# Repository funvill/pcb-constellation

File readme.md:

# LED Constellation Star map

This project is part of the [2023 100 ideas project](https://blog.abluestar.com/projects/2023-100-ideas/), [Idea 012 - LED Constellation Star map](https://blog.abluestar.com/idea012-led-constellation-star-map/)

The idea is to have a map of constellations using addressable RGB LEDs for the stars. Then program the LEDs so that they twinkle, and the brightness and color temperature matches the corresponding star.

I originally started this project thinking it would be an easy 4 hour, one night project but it ended up taking 8 hours. The mouse bites took up 4 hours alone.

The board is panelized in such a way that it can be displayed as a single board with data and power lines snaking through the mouse bites. This allows for the entire panel to be displayed as a single board using a single microcontroller.

The constellations can also be broken out of the panel and used individually. Each of the corners have a grounded though hold that can be sewn into garment, and through holes to connect a microcontroller.

There are 88 commonly recognizable constellations. I could not fit all the constellations on a single board with a reasonable price. I arbitrarily selected 19 constellations in the northern hemisphere that I liked.

As always open to suggestions

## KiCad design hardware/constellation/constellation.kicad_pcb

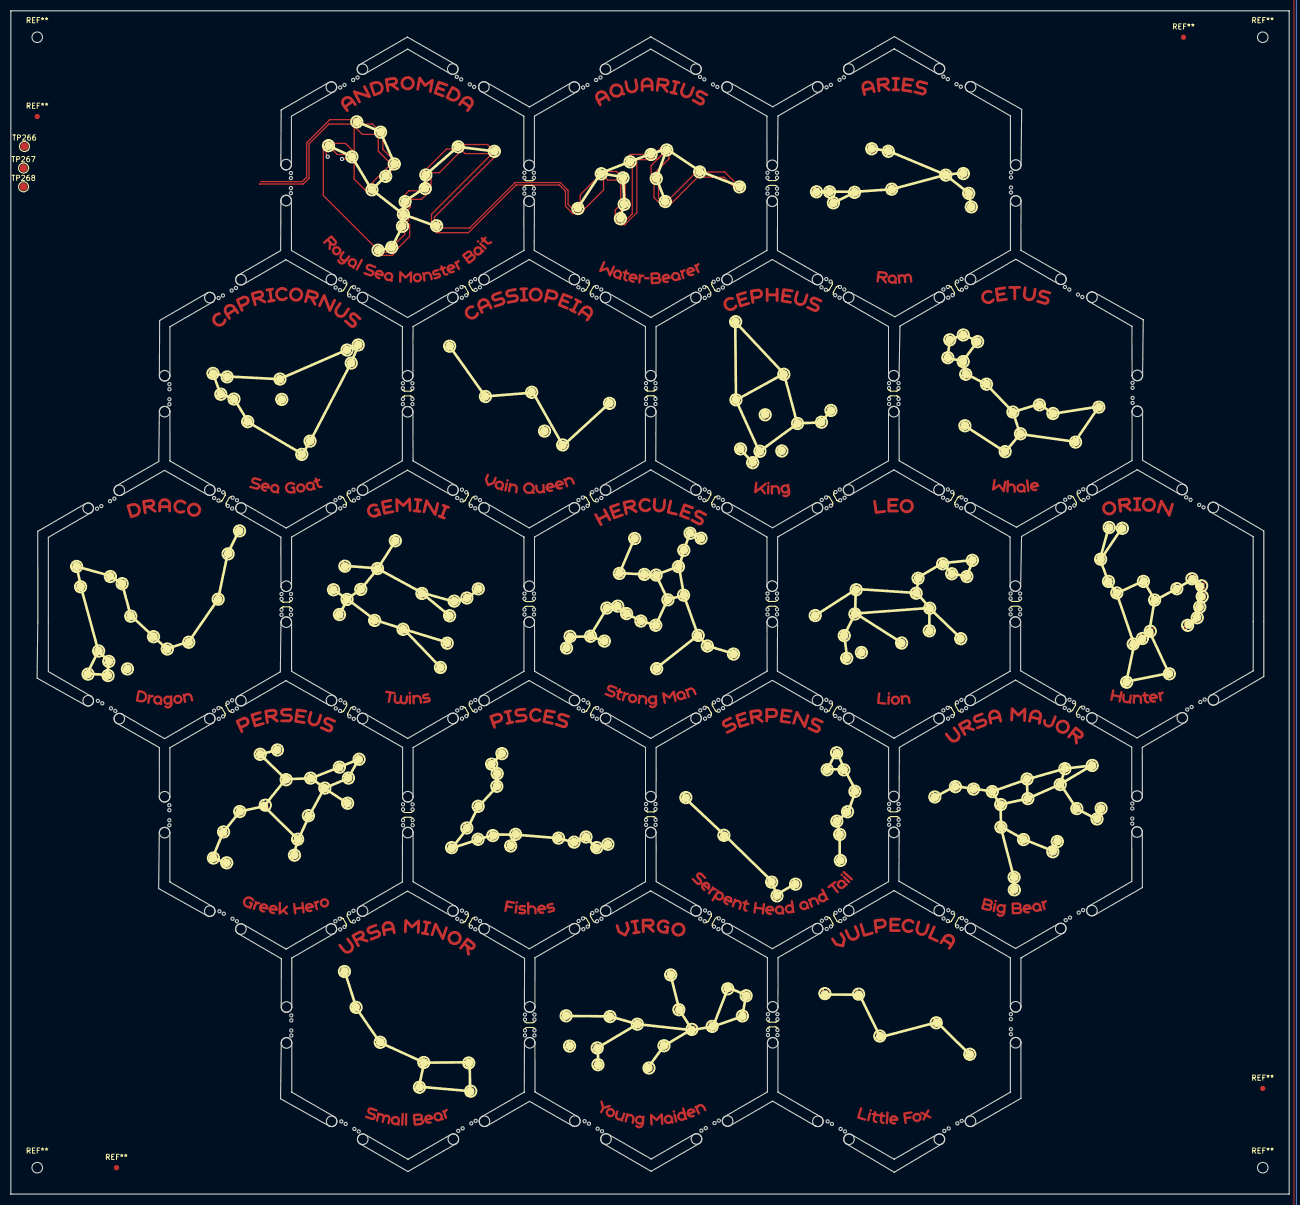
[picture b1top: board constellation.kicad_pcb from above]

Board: 2 copper layers, 242.0 x 224.0 mm, 339 parts (0 on the bottom side), 267 nets.

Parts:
TP266, TP267, TP268: TestPoint; TestPoint_Pad_D1.5mm
U1, U2, U3, U4, U5, U6, U7, U8, U9, U10, U11, U12, U13, U14, U15, U16, U17, U18, U19, U20, U21, U22, U23, U24, U25, U26, U27, U28, U29, U30, U31, U32, U33, U34, U35, U36, U37, U38, U39, U40, U41, U42, U43, U44, U45, U46, U47, U48, U49, U50, U51, U52, U53, U54, U55, U56, U57, U58, U59, U60, U61, U62, U63, U64, U65, U66, U67, U68, U69, U70, U71, U72, U73, U74, U75, U76, U77, U78, U79, U80, U81, U82, U83, U84, U85, U86, U87, U88, U89, U90, U91, U92, U93, U94, U95, U96, U97, U98, U99, U100, U101, U102, U103, U104, U105, U106, U107, U108, U109, U110, U111, U112, U113, U114, U115, U116, U117, U118, U119, U120, U121, U122, U123, U124, U125, U126, U127, U128, U129, U130, U131, U132, U133, U134, U135, U136, U137, U138, U139, U140, U141, U142, U143, U144, U145, U146, U147, U148, U149, U150, U151, U152, U153, U154, U155, U156, U157, U158, U159, U160, U161, U162, U163, U164, U165, U166, U167, U168, U169, U170, U171, U172, U173, U174, U175, U176, U177, U178, U179, U180, U181, U182, U183, U184, U185, U186, U187, U188, U189, U190, U191, U192, U193, U194, U195, U196, U197, U198, U199, U200, U201, U202, U203, U204, U205, U206, U207, U208, U209, U210, U211, U212, U213, U214, U215, U216, U217, U218, U219, U220, U221, U222, U223, U224, U225, U226, U227, U228, U229, U230, U231, U232, U233, U234, U235, U236, U237, U238, U239, U240, U241, U242, U243, U244, U245, U246, U247, U248, U249, U250, U251, U252, U253, U254, U255, U256, U257, U258, U259, U260, U261, U262, U263, U264, U265, U266: XL-1010RGBC; LED-SMD_4P-L1.0-W1.0-TL_XL-1010RGBC-WS2812B
mouse-bite-2mm-slot, mouse-bite-2mm-slot#2, mouse-bite-2mm-slot#8, mouse-bite-2mm-slot#14, mouse-bite-2mm-slot#17, mouse-bite-2mm-slot#18, mouse-bite-2mm-slot#22, mouse-bite-2mm-slot#25, mouse-bite-2mm-slot#28, mouse-bite-2mm-slot#29, mouse-bite-2mm-slot#30, mouse-bite-2mm-slot#33, mouse-bite-2mm-slot#36, mouse-bite-2mm-slot#40, mouse-bite-2mm-slot#41, mouse-bite-2mm-slot#43, mouse-bite-2mm-slot#45, mouse-bite-2mm-slot#47, mouse-bite-2mm-slot#48, mouse-bite-2mm-slot#50, mouse-bite-2mm-slot#56, mouse-bite-2mm-slot#57, mouse-bite-2mm-slot#61, mouse-bite-2mm-slot#64, mouse-bite-2mm-slot#65, mouse-bite-2mm-slot#67, mouse-bite-2mm-slot#68, mouse-bite-2mm-slot#70: VAL**; mouse-bite-2mm-slot_edge
mouse-bite-2mm-slot#3, mouse-bite-2mm-slot#4, mouse-bite-2mm-slot#5, mouse-bite-2mm-slot#6, mouse-bite-2mm-slot#7, mouse-bite-2mm-slot#9, mouse-bite-2mm-slot#10, mouse-bite-2mm-slot#11, mouse-bite-2mm-slot#12, mouse-bite-2mm-slot#13, mouse-bite-2mm-slot#15, mouse-bite-2mm-slot#16, mouse-bite-2mm-slot#19, mouse-bite-2mm-slot#20, mouse-bite-2mm-slot#21, mouse-bite-2mm-slot#23, mouse-bite-2mm-slot#24, mouse-bite-2mm-slot#26, mouse-bite-2mm-slot#27, mouse-bite-2mm-slot#31, mouse-bite-2mm-slot#32, mouse-bite-2mm-slot#34, mouse-bite-2mm-slot#35, mouse-bite-2mm-slot#37, mouse-bite-2mm-slot#38, mouse-bite-2mm-slot#39, mouse-bite-2mm-slot#42, mouse-bite-2mm-slot#44, mouse-bite-2mm-slot#46, mouse-bite-2mm-slot#49, mouse-bite-2mm-slot#51, mouse-bite-2mm-slot#52, mouse-bite-2mm-slot#53, mouse-bite-2mm-slot#54, mouse-bite-2mm-slot#55, mouse-bite-2mm-slot#58, mouse-bite-2mm-slot#59, mouse-bite-2mm-slot#60, mouse-bite-2mm-slot#62, mouse-bite-2mm-slot#63, mouse-bite-2mm-slot#66, mouse-bite-2mm-slot#69: VAL**; mouse-bite-2mm-slot_1

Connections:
+5V: U1.2 (VDD), U2.2 (VDD), U3.2 (VDD), U4.2 (VDD), U5.2 (VDD), U6.2 (VDD), U7.2 (VDD), U8.2 (VDD), U9.2 (VDD), U10.2 (VDD), U11.2 (VDD), U12.2 (VDD), U13.2 (VDD), U14.2 (VDD), U15.2 (VDD), U16.2 (VDD), U17.2 (VDD), U18.2 (VDD), U19.2 (VDD), U20.2 (VDD), U21.2 (VDD), U22.2 (VDD), U23.2 (VDD), U24.2 (VDD), U25.2 (VDD), U26.2 (VDD), U27.2 (VDD), U28.2 (VDD), U29.2 (VDD), U30.2 (VDD), U31.2 (VDD), U32.2 (VDD), U33.2 (VDD), U34.2 (VDD), U35.2 (VDD), U36.2 (VDD), U37.2 (VDD), U38.2 (VDD), U39.2 (VDD), U40.2 (VDD), U41.2 (VDD), U42.2 (VDD), U43.2 (VDD), U44.2 (VDD), U45.2 (VDD), U46.2 (VDD), U47.2 (VDD), U48.2 (VDD), U49.2 (VDD), U50.2 (VDD), U51.2 (VDD), U52.2 (VDD), U53.2 (VDD), U54.2 (VDD), U55.2 (VDD), U56.2 (VDD), U57.2 (VDD), U58.2 (VDD), U59.2 (VDD), U60.2 (VDD), U61.2 (VDD), U62.2 (VDD), U63.2 (VDD), U64.2 (VDD), U65.2 (VDD), U66.2 (VDD), U67.2 (VDD), U68.2 (VDD), U69.2 (VDD), U70.2 (VDD), U71.2 (VDD), U72.2 (VDD), U73.2 (VDD), U74.2 (VDD), U75.2 (VDD), U76.2 (VDD), U77.2 (VDD), U78.2 (VDD), U79.2 (VDD), U80.2 (VDD), U81.2 (VDD), U82.2 (VDD), U83.2 (VDD), U84.2 (VDD), U85.2 (VDD), U86.2 (VDD), U87.2 (VDD), U88.2 (VDD), U89.2 (VDD), U90.2 (VDD), U91.2 (VDD), U92.2 (VDD), U93.2 (VDD), U94.2 (VDD), U95.2 (VDD), U96.2 (VDD), U97.2 (VDD), U98.2 (VDD), U99.2 (VDD), U100.2 (VDD), U101.2 (VDD), U102.2 (VDD), U103.2 (VDD), U104.2 (VDD), U105.2 (VDD), U106.2 (VDD), U107.2 (VDD), U108.2 (VDD), U109.2 (VDD), U110.2 (VDD), U111.2 (VDD), U112.2 (VDD), U113.2 (VDD), U114.2 (VDD), U115.2 (VDD), U116.2 (VDD), U117.2 (VDD), U118.2 (VDD), U119.2 (VDD), U120.2 (VDD), U121.2 (VDD), U122.2 (VDD), U123.2 (VDD), U124.2 (VDD), U125.2 (VDD), U126.2 (VDD), U127.2 (VDD), U128.2 (VDD), U129.2 (VDD), U130.2 (VDD), U131.2 (VDD), U132.2 (VDD), U133.2 (VDD), U134.2 (VDD), U135.2 (VDD), U136.2 (VDD), U137.2 (VDD), U138.2 (VDD), U139.2 (VDD), U140.2 (VDD), U141.2 (VDD), U142.2 (VDD), U143.2 (VDD), U144.2 (VDD), U145.2 (VDD), U146.2 (VDD), U147.2 (VDD), U148.2 (VDD), U149.2 (VDD), U150.2 (VDD), U151.2 (VDD), U152.2 (VDD), U153.2 (VDD), U154.2 (VDD), U155.2 (VDD), U156.2 (VDD), U157.2 (VDD), U158.2 (VDD), U159.2 (VDD), U160.2 (VDD), U161.2 (VDD), U162.2 (VDD), U163.2 (VDD), U164.2 (VDD), U165.2 (VDD), U166.2 (VDD), U167.2 (VDD), U168.2 (VDD), U169.2 (VDD), U170.2 (VDD), U171.2 (VDD), U172.2 (VDD), U173.2 (VDD), U174.2 (VDD), U175.2 (VDD), U176.2 (VDD), U177.2 (VDD), U178.2 (VDD), U179.2 (VDD), U180.2 (VDD), U181.2 (VDD), U182.2 (VDD), U183.2 (VDD), U184.2 (VDD), U185.2 (VDD), U186.2 (VDD), U187.2 (VDD), U188.2 (VDD), U189.2 (VDD), U190.2 (VDD), U191.2 (VDD), U192.2 (VDD), U193.2 (VDD), U194.2 (VDD), U195.2 (VDD), U196.2 (VDD), U197.2 (VDD), U198.2 (VDD), U199.2 (VDD), U200.2 (VDD), U201.2 (VDD), U202.2 (VDD), U203.2 (VDD), U204.2 (VDD), U205.2 (VDD), U206.2 (VDD), U207.2 (VDD), U208.2 (VDD), U209.2 (VDD), U210.2 (VDD), U211.2 (VDD), U212.2 (VDD), U213.2 (VDD), U214.2 (VDD), U215.2 (VDD), U216.2 (VDD), U217.2 (VDD), U218.2 (VDD), U219.2 (VDD), U220.2 (VDD), U221.2 (VDD), U222.2 (VDD), U223.2 (VDD), U224.2 (VDD), U225.2 (VDD), U226.2 (VDD), U227.2 (VDD), U228.2 (VDD), U229.2 (VDD), U230.2 (VDD), U231.2 (VDD), U232.2 (VDD), U233.2 (VDD), U234.2 (VDD), U235.2 (VDD), U236.2 (VDD), U237.2 (VDD), U238.2 (VDD), U239.2 (VDD), U240.2 (VDD), U241.2 (VDD), U242.2 (VDD), U243.2 (VDD), U244.2 (VDD), U245.2 (VDD), U246.2 (VDD), U247.2 (VDD), U248.2 (VDD), U249.2 (VDD), U250.2 (VDD), U251.2 (VDD), U252.2 (VDD), U253.2 (VDD), U254.2 (VDD), U255.2 (VDD), U256.2 (VDD), U257.2 (VDD), U258.2 (VDD), U259.2 (VDD), U260.2 (VDD), U261.2 (VDD), U262.2 (VDD), U263.2 (VDD), U264.2 (VDD), U265.2 (VDD), U266.2 (VDD)
GND: U1.3 (GND), U2.3 (GND), U3.3 (GND), U4.3 (GND), U5.3 (GND), U6.3 (GND), U7.3 (GND), U8.3 (GND), U9.3 (GND), U10.3 (GND), U11.3 (GND), U12.3 (GND), U13.3 (GND), U14.3 (GND), U15.3 (GND), U16.3 (GND), U17.3 (GND), U18.3 (GND), U19.3 (GND), U20.3 (GND), U21.3 (GND), U22.3 (GND), U23.3 (GND), U24.3 (GND), U25.3 (GND), U26.3 (GND), U27.3 (GND), U28.3 (GND), U29.3 (GND), U30.3 (GND), U31.3 (GND), U32.3 (GND), U33.3 (GND), U34.3 (GND), U35.3 (GND), U36.3 (GND), U37.3 (GND), U38.3 (GND), U39.3 (GND), U40.3 (GND), U41.3 (GND), U42.3 (GND), U43.3 (GND), U44.3 (GND), U45.3 (GND), U46.3 (GND), U47.3 (GND), U48.3 (GND), U49.3 (GND), U50.3 (GND), U51.3 (GND), U52.3 (GND), U53.3 (GND), U54.3 (GND), U55.3 (GND), U56.3 (GND), U57.3 (GND), U58.3 (GND), U59.3 (GND), U60.3 (GND), U61.3 (GND), U62.3 (GND), U63.3 (GND), U64.3 (GND), U65.3 (GND), U66.3 (GND), U67.3 (GND), U68.3 (GND), U69.3 (GND), U70.3 (GND), U71.3 (GND), U72.3 (GND), U73.3 (GND), U74.3 (GND), U75.3 (GND), U76.3 (GND), U77.3 (GND), U78.3 (GND), U79.3 (GND), U80.3 (GND), U81.3 (GND), U82.3 (GND), U83.3 (GND), U84.3 (GND), U85.3 (GND), U86.3 (GND), U87.3 (GND), U88.3 (GND), U89.3 (GND), U90.3 (GND), U91.3 (GND), U92.3 (GND), U93.3 (GND), U94.3 (GND), U95.3 (GND), U96.3 (GND), U97.3 (GND), U98.3 (GND), U99.3 (GND), U100.3 (GND), U101.3 (GND), U102.3 (GND), U103.3 (GND), U104.3 (GND), U105.3 (GND), U106.3 (GND), U107.3 (GND), U108.3 (GND), U109.3 (GND), U110.3 (GND), U111.3 (GND), U112.3 (GND), U113.3 (GND), U114.3 (GND), U115.3 (GND), U116.3 (GND), U117.3 (GND), U118.3 (GND), U119.3 (GND), U120.3 (GND), U121.3 (GND), U122.3 (GND), U123.3 (GND), U124.3 (GND), U125.3 (GND), U126.3 (GND), U127.3 (GND), U128.3 (GND), U129.3 (GND), U130.3 (GND), U131.3 (GND), U132.3 (GND), U133.3 (GND), U134.3 (GND), U135.3 (GND), U136.3 (GND), U137.3 (GND), U138.3 (GND), U139.3 (GND), U140.3 (GND), U141.3 (GND), U142.3 (GND), U143.3 (GND), U144.3 (GND), U145.3 (GND), U146.3 (GND), U147.3 (GND), U148.3 (GND), U149.3 (GND), U150.3 (GND), U151.3 (GND), U152.3 (GND), U153.3 (GND), U154.3 (GND), U155.3 (GND), U156.3 (GND), U157.3 (GND), U158.3 (GND), U159.3 (GND), U160.3 (GND), U161.3 (GND), U162.3 (GND), U163.3 (GND), U164.3 (GND), U165.3 (GND), U166.3 (GND), U167.3 (GND), U168.3 (GND), U169.3 (GND), U170.3 (GND), U171.3 (GND), U172.3 (GND), U173.3 (GND), U174.3 (GND), U175.3 (GND), U176.3 (GND), U177.3 (GND), U178.3 (GND), U179.3 (GND), U180.3 (GND), U181.3 (GND), U182.3 (GND), U183.3 (GND), U184.3 (GND), U185.3 (GND), U186.3 (GND), U187.3 (GND), U188.3 (GND), U189.3 (GND), U190.3 (GND), U191.3 (GND), U192.3 (GND), U193.3 (GND), U194.3 (GND), U195.3 (GND), U196.3 (GND), U197.3 (GND), U198.3 (GND), U199.3 (GND), U200.3 (GND), U201.3 (GND), U202.3 (GND), U203.3 (GND), U204.3 (GND), U205.3 (GND), U206.3 (GND), U207.3 (GND), U208.3 (GND), U209.3 (GND), U210.3 (GND), U211.3 (GND), U212.3 (GND), U213.3 (GND), U214.3 (GND), U215.3 (GND), U216.3 (GND), U217.3 (GND), U218.3 (GND), U219.3 (GND), U220.3 (GND), U221.3 (GND), U222.3 (GND), U223.3 (GND), U224.3 (GND), U225.3 (GND), U226.3 (GND), U227.3 (GND), U228.3 (GND), U229.3 (GND), U230.3 (GND), U231.3 (GND), U232.3 (GND), U233.3 (GND), U234.3 (GND), U235.3 (GND), U236.3 (GND), U237.3 (GND), U238.3 (GND), U239.3 (GND), U240.3 (GND), U241.3 (GND), U242.3 (GND), U243.3 (GND), U244.3 (GND), U245.3 (GND), U246.3 (GND), U247.3 (GND), U248.3 (GND), U249.3 (GND), U250.3 (GND), U251.3 (GND), U252.3 (GND), U253.3 (GND), U254.3 (GND), U255.3 (GND), U256.3 (GND), U257.3 (GND), U258.3 (GND), U259.3 (GND), U260.3 (GND), U261.3 (GND), U262.3 (GND), U263.3 (GND), U264.3 (GND), U265.3 (GND), U266.3 (GND)
LED_Aquarius: U17.1 (DOUT), U18.4 (DIN)
LED_Aries: U29.1 (DOUT), U30.4 (DIN)
LED_Capricornus: U72.1 (DOUT), U73.4 (DIN)
LED_Cassiopeia: U66.1 (DOUT), U67.4 (DIN)
LED_Cepheus: U55.1 (DOUT), U56.4 (DIN)
LED_Cetus: U40.1 (DOUT), U41.4 (DIN)
LED_Draco: U84.1 (DOUT), U85.4 (DIN)
LED_Gemini: U100.1 (DOUT), U101.4 (DIN)
LED_Hercules: U116.1 (DOUT), U117.4 (DIN)
LED_Leo: U139.1 (DOUT), U140.4 (DIN)
LED_Orion: U155.1 (DOUT), U156.4 (DIN)
LED_Perseus: U222.1 (DOUT), U223.4 (DIN)
LED_Pisces: U206.1 (DOUT), U207.4 (DIN)
LED_Serpens: U193.1 (DOUT), U194.4 (DIN)
LED_Ursa_major: U174.1 (DOUT), U175.4 (DIN)
LED_Ursa_minor: U239.1 (DOUT), U240.4 (DIN)
LED_Virgo: U246.1 (DOUT), U247.4 (DIN)
LED_Vulpecula: U261.1 (DOUT), U262.4 (DIN)
unnamed: U1.1 (DOUT), U2.4 (DIN)
unnamed: U2.1 (DOUT), U3.4 (DIN)
unnamed: U3.1 (DOUT), U4.4 (DIN)
unnamed: U4.1 (DOUT), U5.4 (DIN)
unnamed: U5.1 (DOUT), U6.4 (DIN)
unnamed: U6.1 (DOUT), U7.4 (DIN)
unnamed: U7.1 (DOUT), U8.4 (DIN)
unnamed: U8.1 (DOUT), U9.4 (DIN)
unnamed: U9.1 (DOUT), U10.4 (DIN)
unnamed: U10.1 (DOUT), U11.4 (DIN)
unnamed: U11.1 (DOUT), U12.4 (DIN)
unnamed: U12.1 (DOUT), U13.4 (DIN)
unnamed: U13.1 (DOUT), U14.4 (DIN)
unnamed: U14.1 (DOUT), U15.4 (DIN)
unnamed: U15.1 (DOUT), U16.4 (DIN)
unnamed: U16.1 (DOUT), U17.4 (DIN)
unnamed: U18.1 (DOUT), U19.4 (DIN)
unnamed: U19.1 (DOUT), U20.4 (DIN)
unnamed: U20.1 (DOUT), U21.4 (DIN)
unnamed: U21.1 (DOUT), U22.4 (DIN)
unnamed: U22.1 (DOUT), U23.4 (DIN)
unnamed: U23.1 (DOUT), U24.4 (DIN)
unnamed: U24.1 (DOUT), U25.4 (DIN)
unnamed: U25.1 (DOUT), U26.4 (DIN)
unnamed: U26.1 (DOUT), U27.4 (DIN)
unnamed: U27.1 (DOUT), U28.4 (DIN)
unnamed: U28.1 (DOUT), U29.4 (DIN)
unnamed: U30.1 (DOUT), U31.4 (DIN)
unnamed: U31.1 (DOUT), U32.4 (DIN)
unnamed: U32.1 (DOUT), U33.4 (DIN)
unnamed: U33.1 (DOUT), U34.4 (DIN)
unnamed: U34.1 (DOUT), U35.4 (DIN)
unnamed: U35.1 (DOUT), U36.4 (DIN)
unnamed: U36.1 (DOUT), U37.4 (DIN)
unnamed: U37.1 (DOUT), U38.4 (DIN)
unnamed: U38.1 (DOUT), U39.4 (DIN)
unnamed: U39.1 (DOUT), U40.4 (DIN)
unnamed: U41.1 (DOUT), U42.4 (DIN)
unnamed: U42.1 (DOUT), U43.4 (DIN)
unnamed: U43.1 (DOUT), U44.4 (DIN)
unnamed: U44.1 (DOUT), U45.4 (DIN)
unnamed: U45.1 (DOUT), U46.4 (DIN)
unnamed: U46.1 (DOUT), U47.4 (DIN)
unnamed: U47.1 (DOUT), U48.4 (DIN)
unnamed: U48.1 (DOUT), U49.4 (DIN)
unnamed: U49.1 (DOUT), U50.4 (DIN)
unnamed: U50.1 (DOUT), U51.4 (DIN)
unnamed: U51.1 (DOUT), U52.4 (DIN)
unnamed: U52.1 (DOUT), U53.4 (DIN)
unnamed: U53.1 (DOUT), U54.4 (DIN)
unnamed: U54.1 (DOUT), U55.4 (DIN)
unnamed: U56.1 (DOUT), U57.4 (DIN)
unnamed: U57.1 (DOUT), U58.4 (DIN)
unnamed: U58.1 (DOUT), U59.4 (DIN)
unnamed: U59.1 (DOUT), U60.4 (DIN)
unnamed: U60.1 (DOUT), U61.4 (DIN)
unnamed: U61.1 (DOUT), U62.4 (DIN)
unnamed: U62.1 (DOUT), U63.4 (DIN)
unnamed: U63.1 (DOUT), U64.4 (DIN)
unnamed: U64.1 (DOUT), U65.4 (DIN)
unnamed: U65.1 (DOUT), U66.4 (DIN)
unnamed: U67.1 (DOUT), U68.4 (DIN)
unnamed: U68.1 (DOUT), U69.4 (DIN)
unnamed: U69.1 (DOUT), U70.4 (DIN)
unnamed: U70.1 (DOUT), U71.4 (DIN)
unnamed: U71.1 (DOUT), U72.4 (DIN)
unnamed: U73.1 (DOUT), U74.4 (DIN)
unnamed: U74.1 (DOUT), U75.4 (DIN)
unnamed: U75.1 (DOUT), U76.4 (DIN)
unnamed: U76.1 (DOUT), U77.4 (DIN)
unnamed: U77.1 (DOUT), U78.4 (DIN)
unnamed: U78.1 (DOUT), U79.4 (DIN)
unnamed: U79.1 (DOUT), U80.4 (DIN)
unnamed: U80.1 (DOUT), U81.4 (DIN)
unnamed: U81.1 (DOUT), U82.4 (DIN)
unnamed: U82.1 (DOUT), U83.4 (DIN)
unnamed: U83.1 (DOUT), U84.4 (DIN)
unnamed: U85.1 (DOUT), U86.4 (DIN)
unnamed: U86.1 (DOUT), U87.4 (DIN)
unnamed: U87.1 (DOUT), U88.4 (DIN)
unnamed: U88.1 (DOUT), U89.4 (DIN)
unnamed: U89.1 (DOUT), U90.4 (DIN)
unnamed: U90.1 (DOUT), U91.4 (DIN)
unnamed: U91.1 (DOUT), U92.4 (DIN)
unnamed: U92.1 (DOUT), U93.4 (DIN)
unnamed: U93.1 (DOUT), U94.4 (DIN)
unnamed: U94.1 (DOUT), U95.4 (DIN)
unnamed: U95.1 (DOUT), U96.4 (DIN)
unnamed: U96.1 (DOUT), U97.4 (DIN)
unnamed: U97.1 (DOUT), U98.4 (DIN)
unnamed: U98.1 (DOUT), U99.4 (DIN)
unnamed: U99.1 (DOUT), U100.4 (DIN)
unnamed: U101.1 (DOUT), U102.4 (DIN)
unnamed: U102.1 (DOUT), U103.4 (DIN)
unnamed: U103.1 (DOUT), U104.4 (DIN)
unnamed: U104.1 (DOUT), U105.4 (DIN)
unnamed: U105.1 (DOUT), U106.4 (DIN)
unnamed: U106.1 (DOUT), U107.4 (DIN)
unnamed: U107.1 (DOUT), U108.4 (DIN)
unnamed: U108.1 (DOUT), U109.4 (DIN)
unnamed: U109.1 (DOUT), U110.4 (DIN)
unnamed: U110.1 (DOUT), U111.4 (DIN)
unnamed: U111.1 (DOUT), U112.4 (DIN)
unnamed: U112.1 (DOUT), U113.4 (DIN)
unnamed: U113.1 (DOUT), U114.4 (DIN)
unnamed: U114.1 (DOUT), U115.4 (DIN)
unnamed: U115.1 (DOUT), U116.4 (DIN)
unnamed: U117.1 (DOUT), U118.4 (DIN)
unnamed: U118.1 (DOUT), U119.4 (DIN)
unnamed: U119.1 (DOUT), U120.4 (DIN)
unnamed: U120.1 (DOUT), U121.4 (DIN)
unnamed: U121.1 (DOUT), U122.4 (DIN)
unnamed: U122.1 (DOUT), U123.4 (DIN)
unnamed: U123.1 (DOUT), U124.4 (DIN)
unnamed: U124.1 (DOUT), U125.4 (DIN)
unnamed: U125.1 (DOUT), U126.4 (DIN)
unnamed: U126.1 (DOUT), U127.4 (DIN)
unnamed: U127.1 (DOUT), U128.4 (DIN)
unnamed: U128.1 (DOUT), U129.4 (DIN)
unnamed: U129.1 (DOUT), U130.4 (DIN)
unnamed: U130.1 (DOUT), U131.4 (DIN)
unnamed: U131.1 (DOUT), U132.4 (DIN)
unnamed: U132.1 (DOUT), U133.4 (DIN)
unnamed: U133.1 (DOUT), U134.4 (DIN)
unnamed: U134.1 (DOUT), U135.4 (DIN)
unnamed: U135.1 (DOUT), U136.4 (DIN)
unnamed: U136.1 (DOUT), U137.4 (DIN)
unnamed: U137.1 (DOUT), U138.4 (DIN)
unnamed: U138.1 (DOUT), U139.4 (DIN)
unnamed: U140.1 (DOUT), U141.4 (DIN)
unnamed: U141.1 (DOUT), U142.4 (DIN)
unnamed: U142.1 (DOUT), U143.4 (DIN)
unnamed: U143.1 (DOUT), U144.4 (DIN)
unnamed: U144.1 (DOUT), U145.4 (DIN)
unnamed: U145.1 (DOUT), U146.4 (DIN)
unnamed: U146.1 (DOUT), U147.4 (DIN)
unnamed: U147.1 (DOUT), U148.4 (DIN)
unnamed: U148.1 (DOUT), U149.4 (DIN)
unnamed: U149.1 (DOUT), U150.4 (DIN)
unnamed: U150.1 (DOUT), U151.4 (DIN)
unnamed: U151.1 (DOUT), U152.4 (DIN)
unnamed: U152.1 (DOUT), U153.4 (DIN)
unnamed: U153.1 (DOUT), U154.4 (DIN)
unnamed: U154.1 (DOUT), U155.4 (DIN)
unnamed: U156.1 (DOUT), U157.4 (DIN)
unnamed: U157.1 (DOUT), U158.4 (DIN)
unnamed: U158.1 (DOUT), U159.4 (DIN)
unnamed: U159.1 (DOUT), U160.4 (DIN)
unnamed: U160.1 (DOUT), U161.4 (DIN)
unnamed: U161.1 (DOUT), U162.4 (DIN)
unnamed: U162.1 (DOUT), U163.4 (DIN)
unnamed: U163.1 (DOUT), U164.4 (DIN)
unnamed: U164.1 (DOUT), U165.4 (DIN)
unnamed: U165.1 (DOUT), U166.4 (DIN)
unnamed: U166.1 (DOUT), U167.4 (DIN)
unnamed: U167.1 (DOUT), U168.4 (DIN)
unnamed: U168.1 (DOUT), U169.4 (DIN)
unnamed: U169.1 (DOUT), U170.4 (DIN)
unnamed: U170.1 (DOUT), U171.4 (DIN)
unnamed: U171.1 (DOUT), U172.4 (DIN)
unnamed: U172.1 (DOUT), U173.4 (DIN)
unnamed: U173.1 (DOUT), U174.4 (DIN)
unnamed: U175.1 (DOUT), U176.4 (DIN)
unnamed: U176.1 (DOUT), U177.4 (DIN)
unnamed: U177.1 (DOUT), U178.4 (DIN)
unnamed: U178.1 (DOUT), U179.4 (DIN)
unnamed: U179.1 (DOUT), U180.4 (DIN)
unnamed: U180.1 (DOUT), U181.4 (DIN)
unnamed: U181.1 (DOUT), U182.4 (DIN)
unnamed: U182.1 (DOUT), U183.4 (DIN)
unnamed: U183.1 (DOUT), U184.4 (DIN)
unnamed: U184.1 (DOUT), U185.4 (DIN)
unnamed: U185.1 (DOUT), U186.4 (DIN)
unnamed: U186.1 (DOUT), U187.4 (DIN)
unnamed: U187.1 (DOUT), U188.4 (DIN)
unnamed: U188.1 (DOUT), U189.4 (DIN)
unnamed: U189.1 (DOUT), U190.4 (DIN)
unnamed: U190.1 (DOUT), U191.4 (DIN)
unnamed: U191.1 (DOUT), U192.4 (DIN)
unnamed: U192.1 (DOUT), U193.4 (DIN)
unnamed: U194.1 (DOUT), U195.4 (DIN)
unnamed: U195.1 (DOUT), U196.4 (DIN)
unnamed: U196.1 (DOUT), U197.4 (DIN)
unnamed: U197.1 (DOUT), U198.4 (DIN)
unnamed: U198.1 (DOUT), U199.4 (DIN)
unnamed: U199.1 (DOUT), U200.4 (DIN)
unnamed: U200.1 (DOUT), U201.4 (DIN)
unnamed: U201.1 (DOUT), U202.4 (DIN)
unnamed: U202.1 (DOUT), U203.4 (DIN)
unnamed: U203.1 (DOUT), U204.4 (DIN)
unnamed: U204.1 (DOUT), U205.4 (DIN)
unnamed: U205.1 (DOUT), U206.4 (DIN)
unnamed: U207.1 (DOUT), U208.4 (DIN)
unnamed: U208.1 (DOUT), U209.4 (DIN)
unnamed: U209.1 (DOUT), U210.4 (DIN)
unnamed: U210.1 (DOUT), U211.4 (DIN)
unnamed: U211.1 (DOUT), U212.4 (DIN)
unnamed: U212.1 (DOUT), U213.4 (DIN)
unnamed: U213.1 (DOUT), U214.4 (DIN)
unnamed: U214.1 (DOUT), U215.4 (DIN)
unnamed: U215.1 (DOUT), U216.4 (DIN)
unnamed: U216.1 (DOUT), U217.4 (DIN)
unnamed: U217.1 (DOUT), U218.4 (DIN)
unnamed: U218.1 (DOUT), U219.4 (DIN)
unnamed: U219.1 (DOUT), U220.4 (DIN)
unnamed: U220.1 (DOUT), U221.4 (DIN)
unnamed: U221.1 (DOUT), U222.4 (DIN)
unnamed: U223.1 (DOUT), U224.4 (DIN)
unnamed: U224.1 (DOUT), U225.4 (DIN)
unnamed: U225.1 (DOUT), U226.4 (DIN)
unnamed: U226.1 (DOUT), U227.4 (DIN)
unnamed: U227.1 (DOUT), U228.4 (DIN)
unnamed: U228.1 (DOUT), U229.4 (DIN)
unnamed: U229.1 (DOUT), U230.4 (DIN)
unnamed: U230.1 (DOUT), U231.4 (DIN)
unnamed: U231.1 (DOUT), U232.4 (DIN)
unnamed: U232.1 (DOUT), U233.4 (DIN)
unnamed: U233.1 (DOUT), U234.4 (DIN)
unnamed: U234.1 (DOUT), U235.4 (DIN)
unnamed: U235.1 (DOUT), U236.4 (DIN)
unnamed: U236.1 (DOUT), U237.4 (DIN)
unnamed: U237.1 (DOUT), U238.4 (DIN)
unnamed: U238.1 (DOUT), U239.4 (DIN)
unnamed: U240.1 (DOUT), U241.4 (DIN)
unnamed: U241.1 (DOUT), U242.4 (DIN)
unnamed: U242.1 (DOUT), U243.4 (DIN)
unnamed: U243.1 (DOUT), U244.4 (DIN)
unnamed: U244.1 (DOUT), U245.4 (DIN)
unnamed: U245.1 (DOUT), U246.4 (DIN)
unnamed: U247.1 (DOUT), U248.4 (DIN)
unnamed: U248.1 (DOUT), U249.4 (DIN)
unnamed: U249.1 (DOUT), U250.4 (DIN)
unnamed: U250.1 (DOUT), U251.4 (DIN)
unnamed: U251.1 (DOUT), U252.4 (DIN)
unnamed: U252.1 (DOUT), U253.4 (DIN)
unnamed: U253.1 (DOUT), U254.4 (DIN)
unnamed: U254.1 (DOUT), U255.4 (DIN)
unnamed: U255.1 (DOUT), U256.4 (DIN)
unnamed: U256.1 (DOUT), U257.4 (DIN)
unnamed: U257.1 (DOUT), U258.4 (DIN)
unnamed: U258.1 (DOUT), U259.4 (DIN)
unnamed: U259.1 (DOUT), U260.4 (DIN)
unnamed: U260.1 (DOUT), U261.4 (DIN)
unnamed: TP266.1, U262.1 (DOUT), U263.4 (DIN)
unnamed: TP267.1, U263.1 (DOUT), U264.4 (DIN)
unnamed: TP268.1, U264.1 (DOUT), U265.4 (DIN)
unnamed: U265.1 (DOUT), U266.4 (DIN)

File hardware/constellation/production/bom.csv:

Designator,Footprint,Quantity,Value,LCSC Part #
_115,,1,,
"C1, C10, C11, C12, C13, C14, C15, C16, C17, C18, C19, C2, C20, C21, C22, C23, C24, C25, C26, C27, C28, C29, C3, C30, C31, C32, C33, C34, C35, C36, C37, C38, C4, C5, C6, C7, C8, C9",0603,38,10V 10uF,C19702
"J1, J10, J11, J12, J13, J14, J15, J16, J17, J18, J19, J22, J23, J3, J4, J5, J6, J7, J8, J9",PinHeader_1x04_P2.54mm_Vertical,20,Conn_01x04,
"J40, J41",PinHeader_1x07_P2.54mm_Vertical,2,Conn_01x07,
R1,0402,1,R0,C17168
"U1, U10, U100, U101, U102, U103, U104, U105, U106, U107, U108, U109, U11, U110, U111, U112, U113, U114, U115, U116, U117, U118, U119, U12, U120, U121, U122, U123, U124, U125, U126, U127, U128, U129, U13, U130, U131, U132, U133, U134, U135, U136, U137, U138, U139, U14, U140, U141, U142, U143, U144, U145, U146, U147, U148, U149, U15, U150, U151, U152, U153, U154, U155, U156, U157, U158, U159, U16, U160, U161, U162, U163, U164, U165, U166, U167, U168, U169, U17, U170, U171, U172, U173, U174, U175, U176, U177, U178, U179, U18, U180, U181, U182, U183, U184, U185, U186, U187, U188, U189, U19, U190, U191, U192, U193, U194, U195, U196, U197, U198, U199, U2, U20, U200, U201, U202, U203, U204, U205, U206, U207, U208, U209, U21, U210, U211, U212, U213, U214, U215, U216, U217, U218, U219, U22, U220, U221, U222, U223, U224, U225, U226, U227, U228, U229, U23, U230, U231, U232, U233, U234, U235, U236, U237, U238, U239, U24, U240, U241, U242, U243, U244, U245, U246, U247, U248, U249, U25, U250, U251, U252, U253, U254, U255, U256, U257, U258, U259, U26, U260, U261, U262, U263, U264, U265, U266, U27, U28, U29, U3, U30, U31, U32, U33, U34, U35, U36, U37, U38, U39",LED-SMD_4P-L1.0-W1.0-TL_XL-1010RGBC-WS2812B,200,XL-1010RGBC,C5349953
U267,MOUDLE14P-SMD-2.54-21X17.8MM,1,MOUDLE-SEEEDUINO-XIAO,
"U4, U40, U41, U42, U43, U44, U45, U46, U47, U48, U49, U5, U50, U51, U52, U53, U54, U55, U56, U57, U58, U59, U6, U60, U61, U62, U63, U64, U65, U66, U67, U68, U69, U7, U70, U71, U72, U73, U74, U75, U76, U77, U78, U79, U8, U80, U81, U82, U83, U84, U85, U86, U87, U88, U89, U9, U90, U91, U92, U93, U94, U95, U96, U97, U98, U99",LED-SMD_4P-L1.0-W1.0-TL_XL-1010RGBC-WS2812B,66,XL-1010RGBC,C5349953
"mouse-bite-2mm-slot_70, mouse-bite-2mm-slot_69, mouse-bite-2mm-slot_63, mouse-bite-2mm-slot_57, mouse-bite-2mm-slot_54, mouse-bite-2mm-slot_53, mouse-bite-2mm-slot_49, mouse-bite-2mm-slot_46, mouse-bite-2mm-slot_43, mouse-bite-2mm-slot_42, mouse-bite-2mm-slot_41, mouse-bite-2mm-slot_38, mouse-bite-2mm-slot_35, mouse-bite-2mm-slot_31, mouse-bite-2mm-slot_30, mouse-bite-2mm-slot_28, mouse-bite-2mm-slot_26, mouse-bite-2mm-slot_24, mouse-bite-2mm-slot_23, mouse-bite-2mm-slot_21, mouse-bite-2mm-slot_15, mouse-bite-2mm-slot_14, mouse-bite-2mm-slot_10, mouse-bite-2mm-slot_7, mouse-bite-2mm-slot_6, mouse-bite-2mm-slot_4, mouse-bite-2mm-slot_3, mouse-bite-2mm-slot",mouse-bite-2mm-slot_edge,28,VAL**,
"mouse-bite-2mm-slot_68, mouse-bite-2mm-slot_67, mouse-bite-2mm-slot_66, mouse-bite-2mm-slot_65, mouse-bite-2mm-slot_64, mouse-bite-2mm-slot_62, mouse-bite-2mm-slot_61, mouse-bite-2mm-slot_60, mouse-bite-2mm-slot_59, mouse-bite-2mm-slot_58, mouse-bite-2mm-slot_56, mouse-bite-2mm-slot_55, mouse-bite-2mm-slot_52, mouse-bite-2mm-slot_51, mouse-bite-2mm-slot_50, mouse-bite-2mm-slot_48, mouse-bite-2mm-slot_47, mouse-bite-2mm-slot_45, mouse-bite-2mm-slot_44, mouse-bite-2mm-slot_40, mouse-bite-2mm-slot_39, mouse-bite-2mm-slot_37, mouse-bite-2mm-slot_36, mouse-bite-2mm-slot_34, mouse-bite-2mm-slot_33, mouse-bite-2mm-slot_32, mouse-bite-2mm-slot_29, mouse-bite-2mm-slot_27, mouse-bite-2mm-slot_25, mouse-bite-2mm-slot_22, mouse-bite-2mm-slot_20, mouse-bite-2mm-slot_19, mouse-bite-2mm-slot_18, mouse-bite-2mm-slot_17, mouse-bite-2mm-slot_16, mouse-bite-2mm-slot_13, mouse-bite-2mm-slot_12, mouse-bite-2mm-slot_11, mouse-bite-2mm-slot_9, mouse-bite-2mm-slot_8, mouse-bite-2mm-slot_5, mouse-bite-2mm-slot_2",mouse-bite-2mm-slot_1,42,VAL**,

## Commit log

2024-07-03 WIP initial commit
2024-07-03 Added the rest of the constellations
2024-07-03 Added order number and tooling holes
2024-07-04 Roughly placed all the LEDs
2024-07-05 WIP: Connecting paths in constellations PCB
2024-07-07 Finished DRC
2024-07-07 Final touches and updated readme
2024-07-07 Cleaned up the silk screen
2024-07-08 Added Xiao RP2040 footprint
